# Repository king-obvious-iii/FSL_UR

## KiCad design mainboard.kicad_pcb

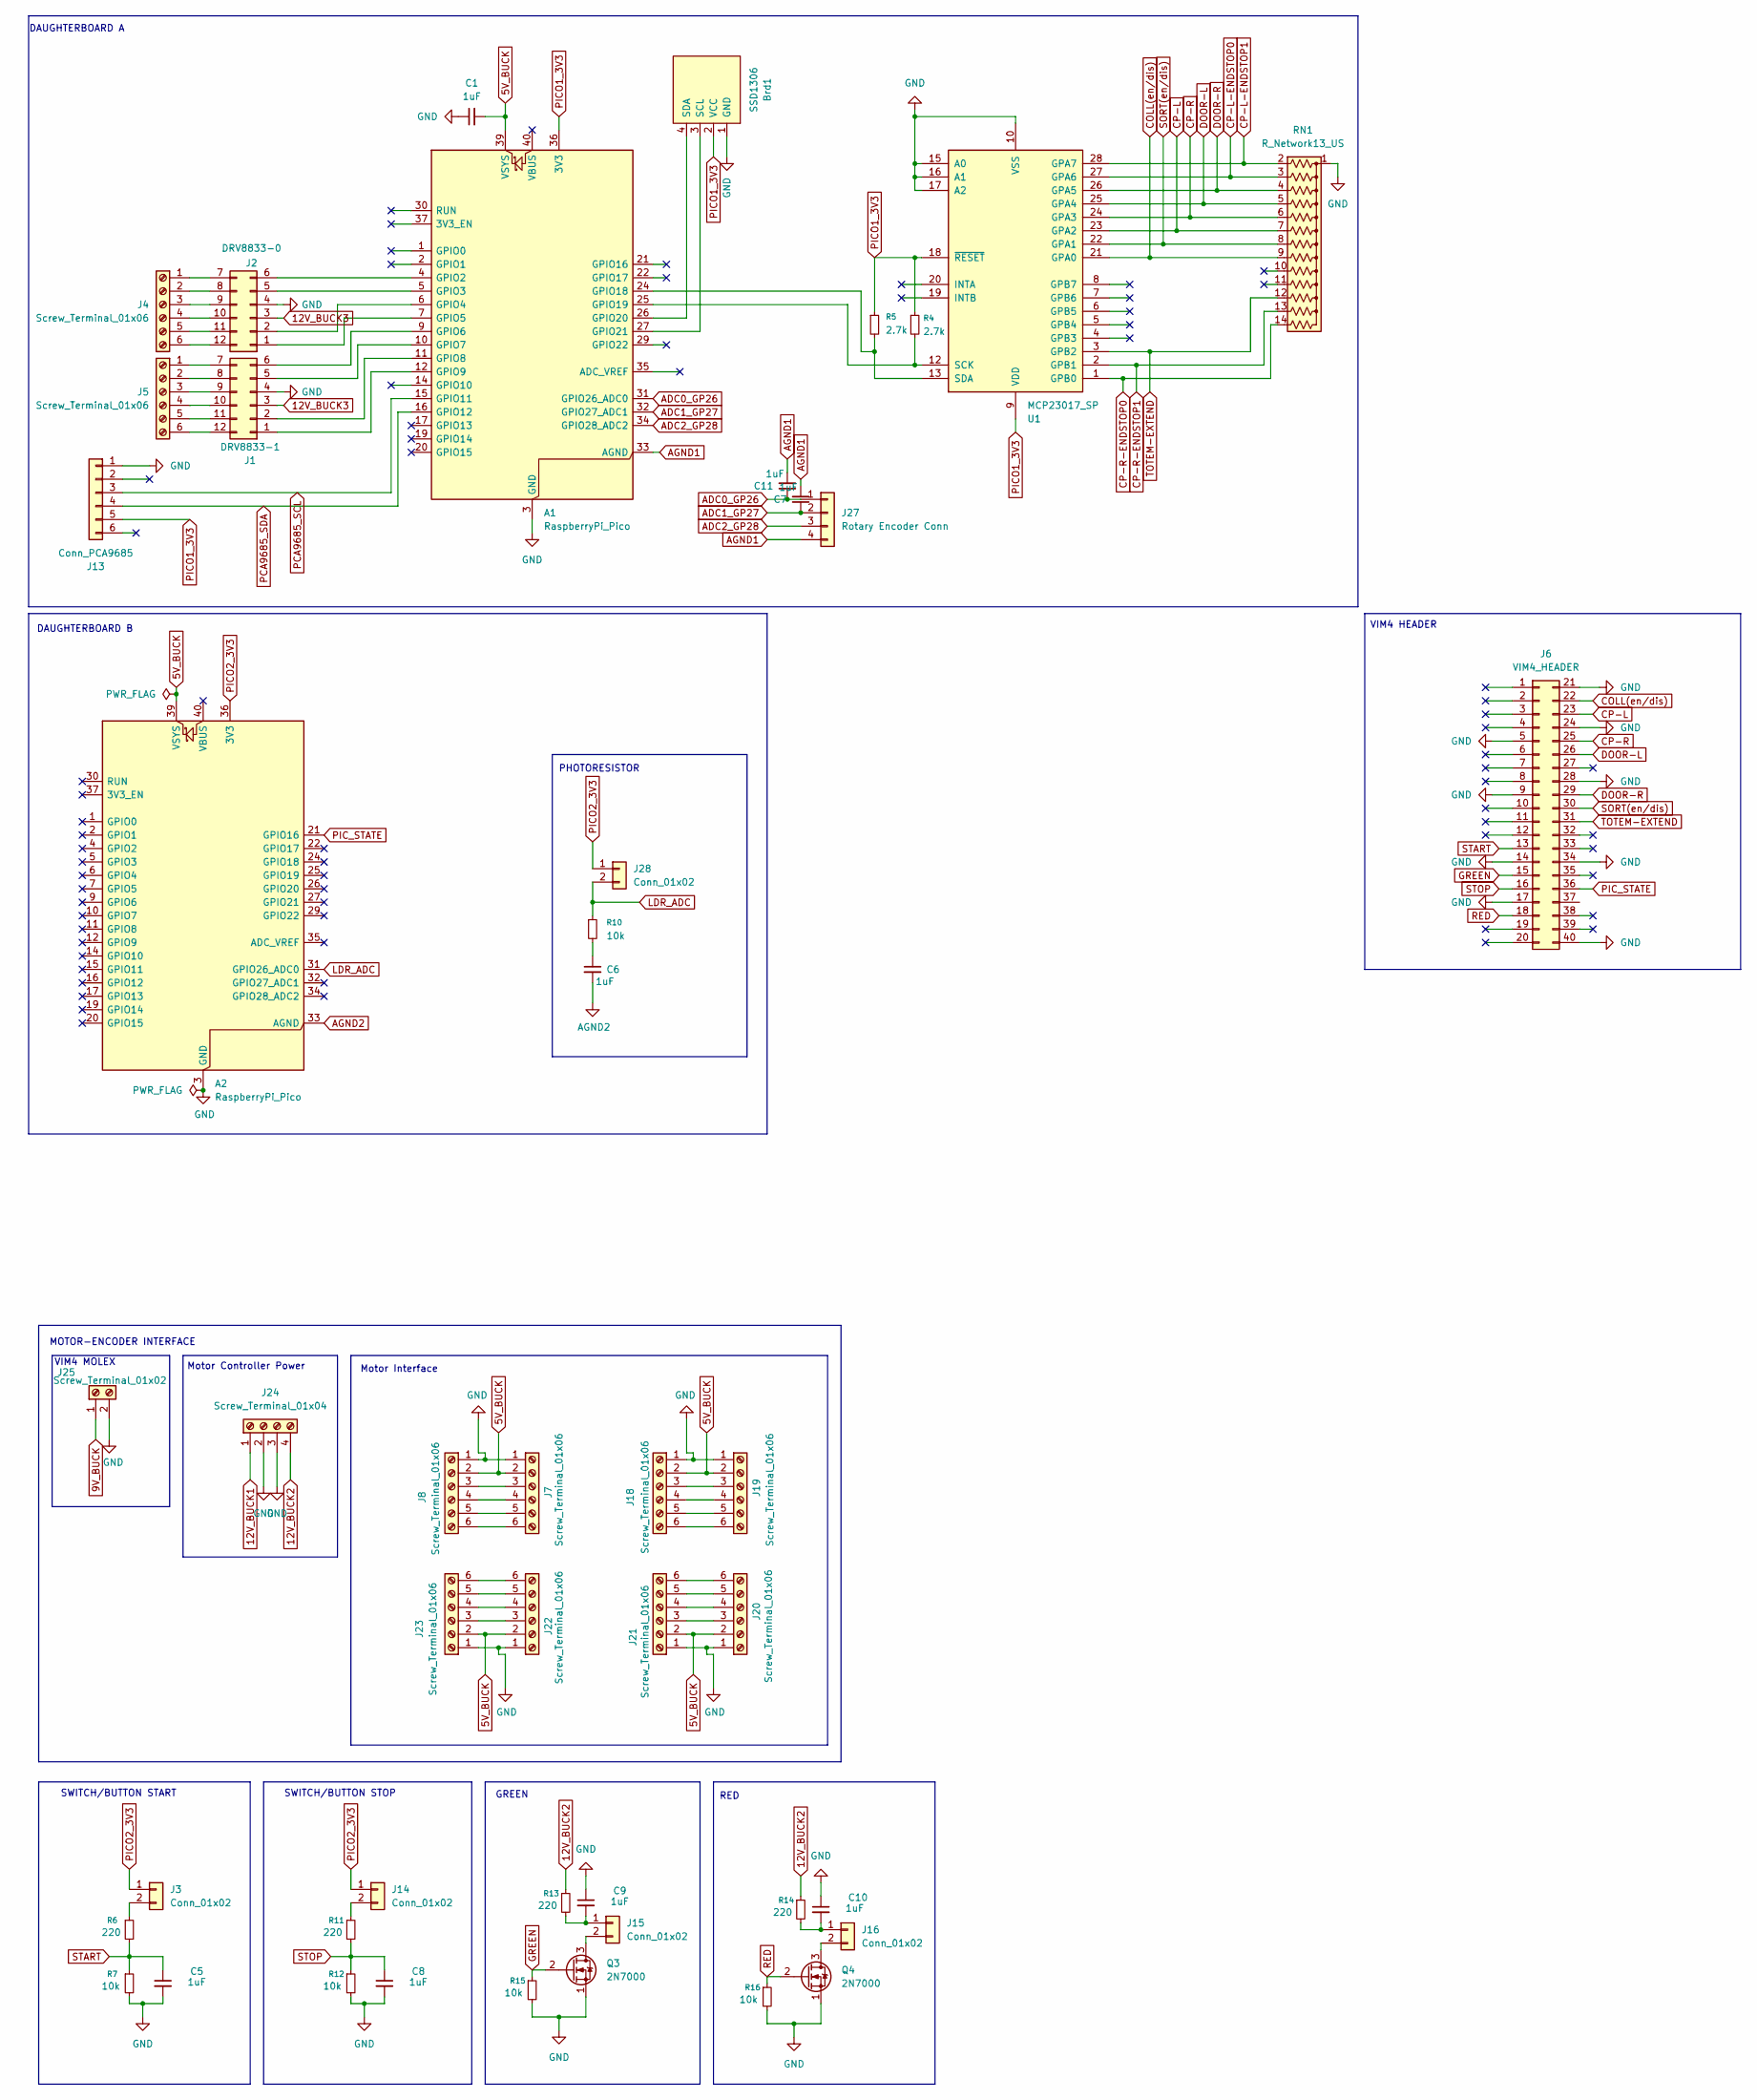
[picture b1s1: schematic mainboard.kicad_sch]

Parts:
A1, A2: RaspberryPi_Pico; RaspberryPi_Pico_Common_Unspecified
Brd1: SSD1306; Molex_KK-254_AE-6410-04A_1x04_P2.54mm_Vertical
C1, C5, C6, C7, C8, C9, C10, C11: 1uF; C_0805_2012Metric
J1: DRV8833-1; DRV8833
J2: DRV8833-0; DRV8833
J3, J14, J15, J16: Conn_01x02; PinHeader_1x02_P2.54mm_Vertical
J4, J5, J7, J8, J18, J19, J20, J21, J22, J23: Screw_Terminal_01x06; TerminalBlock_Xinya_XY308-2.54-6P_1x06_P2.54mm_Horizontal
J6: VIM4_HEADER; IDC-Header_2x20_P2.54mm_Vertical
J13: Conn_PCA9685; JST_EH_B6B-EH-A_1x06_P2.50mm_Vertical
J24: Screw_Terminal_01x04; PinHeader_1x04_P2.54mm_Vertical
J25: Screw_Terminal_01x02; PinHeader_1x02_P2.54mm_Vertical
J27: Rotary Encoder Conn; JST_EH_B4B-EH-A_1x04_P2.50mm_Vertical
J28: Conn_01x02; JST_EH_B2B-EH-A_1x02_P2.50mm_Vertical
Q3, Q4: 2N7000; TO-92_Inline
R4, R5: 2.7k; R_0805_2012Metric
R6, R11, R13, R14: 220; R_0805_2012Metric
R7, R10, R12, R15, R16: 10k; R_0805_2012Metric
RN1: R_Network13_US; DIP-14_W7.62mm
U1: MCP23017_SP; DIP-28_W7.62mm

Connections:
5V_BUCK: A1.39 (VSYS), A2.39 (VSYS), C1.2, J7.2, J8.2, J18.2, J19.2, J20.2, J21.2, J22.2, J23.2; also elsewhere on the board
5V_BUCK2: J13.6
9V_BUCK: J25.1; also elsewhere on the board
12V_BUCK1: J24.1
12V_BUCK2: J24.4, R13.1, R14.1
12V_BUCK3: J1.3, J2.3
ADC0_GP26: A1.31 (GPIO26_ADC0), C11.1, J27.1
ADC1_GP27: A1.32 (GPIO27_ADC1), C7.1, J27.2
ADC2_GP28: A1.34 (GPIO28_ADC2), J27.3
AGND1: A1.33 (AGND), C7.2, C11.2, J27.4
AGND2: A2.33 (AGND), C6.2
COLL(en/dis): J6.22, RN1.9 (R8), U1.21 (GPA0)
CP-L: J6.23, RN1.7 (R6), U1.23 (GPA2)
CP-L-ENDSTOP0: RN1.3 (R2), U1.27 (GPA6); also elsewhere on the board
CP-L-ENDSTOP1: RN1.2 (R1), U1.28 (GPA7); also elsewhere on the board
CP-R: J6.25, RN1.6 (R5), U1.24 (GPA3)
CP-R-ENDSTOP0: RN1.14 (R13), U1.1 (GPB0); also elsewhere on the board
CP-R-ENDSTOP1: RN1.13 (R12), U1.2 (GPB1); also elsewhere on the board
DOOR-L: J6.26, RN1.5 (R4), U1.25 (GPA4)
DOOR-R: J6.29, RN1.4 (R3), U1.26 (GPA5)
GND: A1.3 (GND), A1.8 (GND), A1.13 (GND), A1.18 (GND), A1.23 (GND), A1.28 (GND), A1.38 (GND), A2.3 (GND), A2.8 (GND), A2.13 (GND), A2.18 (GND), A2.23 (GND), A2.28 (GND), A2.38 (GND), Brd1.1 (GND), C1.1, C5.2, C8.2, C9.1, C10.1, J1.4, J2.4, J6.5, J6.9, J6.14, J6.17, J6.21, J6.24, J6.28, J6.34, J6.40, J7.1, J8.1, J13.1, J18.1, J19.1, J20.1, J21.1, J22.1, J23.1, J24.2, J24.3, J25.2, Q3.1 (S), Q4.1 (S), R7.2, R12.2, R15.2, R16.2, RN1.1 (common), U1.10 (VSS), U1.15 (A0), U1.16 (A1), U1.17 (A2); also elsewhere on the board
GREEN: J6.15, Q3.2 (G), R15.1
LDR_ADC: A2.31 (GPIO26_ADC0), J28.2, R10.1
unnamed: A1.4 (GPIO2), J2.6
unnamed: A1.5 (GPIO3), J2.5
unnamed: A1.6 (GPIO4), J2.2
unnamed: A1.7 (GPIO5), J2.1
unnamed: A1.9 (GPIO6), J1.6
unnamed: A1.10 (GPIO7), J1.5
unnamed: A1.11 (GPIO8), J1.2
unnamed: A1.12 (GPIO9), J1.1
unnamed: A1.24 (GPIO18), R5.2, U1.13 (SDA)
unnamed: A1.25 (GPIO19), R4.2, U1.12 (SCK)
unnamed: A1.26 (GPIO20), Brd1.4 (SDA)
unnamed: A1.27 (GPIO21), Brd1.3 (SCL)
unnamed: C6.1, R10.2
unnamed: J1.7, J5.1
unnamed: J1.8, J5.2
unnamed: J1.9, J5.3
unnamed: J1.10, J5.4
unnamed: J1.11, J5.5
unnamed: J1.12, J5.6
unnamed: J2.7, J4.1
unnamed: J2.8, J4.2
unnamed: J2.9, J4.3
unnamed: J2.10, J4.4
unnamed: J2.11, J4.5
unnamed: J2.12, J4.6
unnamed: J3.2, R6.1
unnamed: J7.3, J8.3
unnamed: J7.4, J8.4
unnamed: J7.5, J8.5
unnamed: J7.6, J8.6
unnamed: J14.2, R11.1
unnamed: C9.2, J15.1, R13.2
unnamed: J15.2, Q3.3 (D)
unnamed: C10.2, J16.1, R14.2
unnamed: J16.2, Q4.3 (D)
unnamed: J18.3, J19.3
unnamed: J18.4, J19.4
unnamed: J18.5, J19.5
unnamed: J18.6, J19.6
unnamed: J20.3, J21.3
unnamed: J20.4, J21.4
unnamed: J20.5, J21.5
unnamed: J20.6, J21.6
unnamed: J22.3, J23.3
unnamed: J22.4, J23.4
unnamed: J22.5, J23.5
unnamed: J22.6, J23.6
PCA9685_SCL: A1.15 (GPIO11), J13.3
PCA9685_SDA: A1.16 (GPIO12), J13.4
PIC_STATE: A2.21 (GPIO16), J6.36
RED: J6.18, Q4.2 (G), R16.1
SORT(en/dis): J6.30, RN1.8 (R7), U1.22 (GPA1)
START: C5.1, J6.13, R6.2, R7.1
STOP: C8.1, J6.16, R11.2, R12.1
TOTEM-EXTEND: J6.31, RN1.12 (R11), U1.3 (GPB2)

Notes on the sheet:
DAUGHTERBOARD A
Motor Controller Power
VIM4 MOLEX
PHOTORESISTOR
GREEN
Motor Interface
MOTOR-ENCODER INTERFACE
VIM4 HEADER
RED
DAUGHTERBOARD B
SWITCH/BUTTON STOP
SWITCH/BUTTON START

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
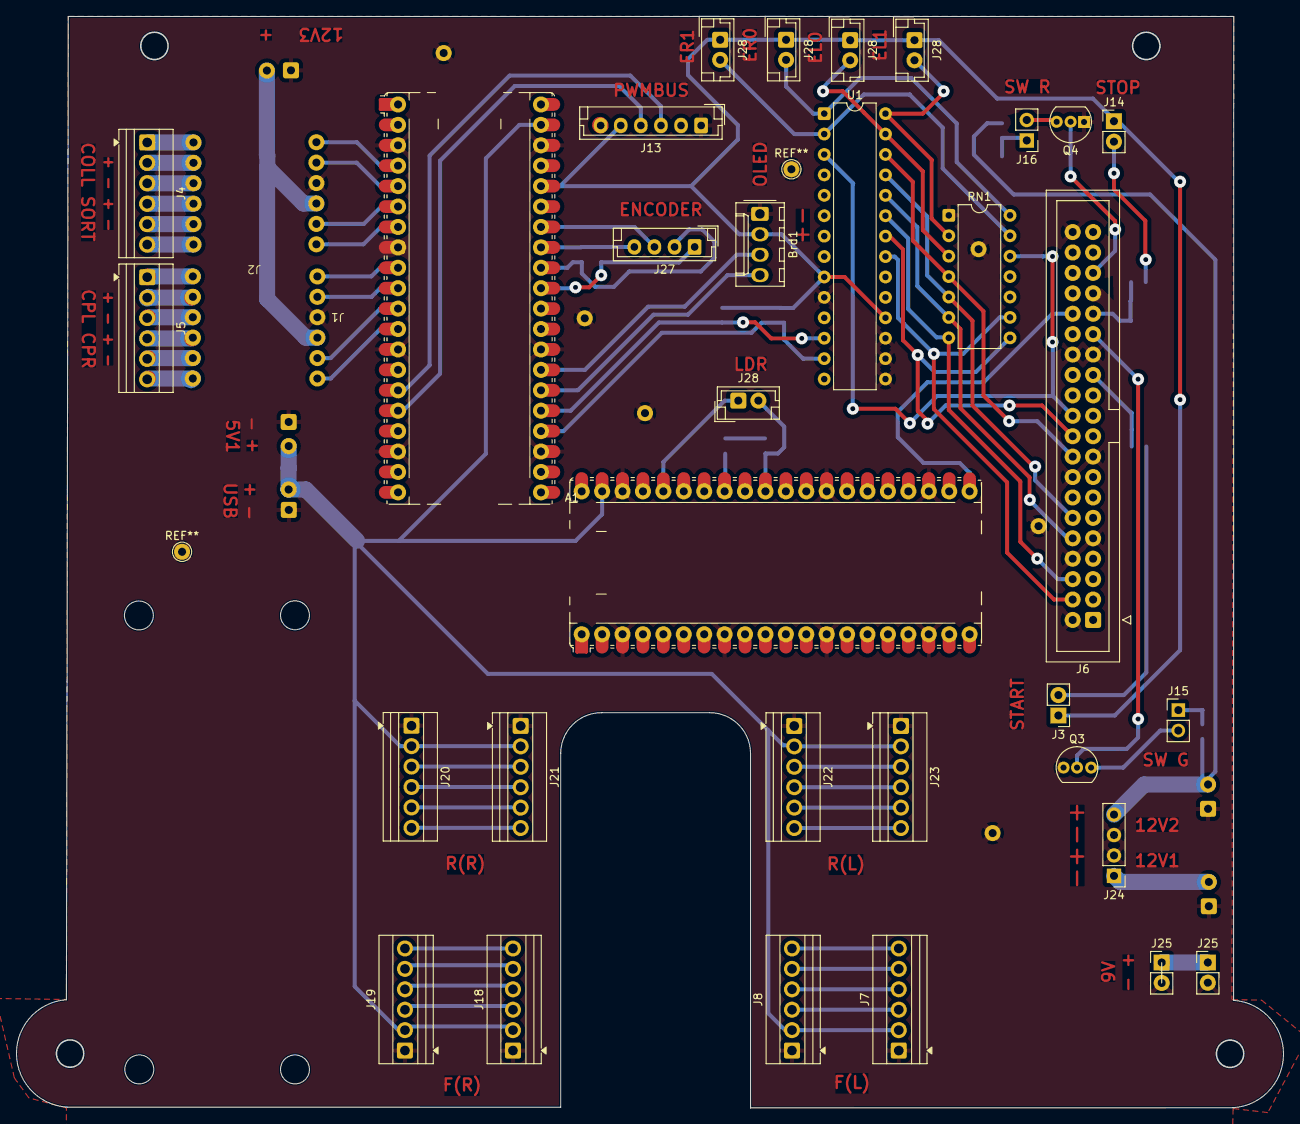
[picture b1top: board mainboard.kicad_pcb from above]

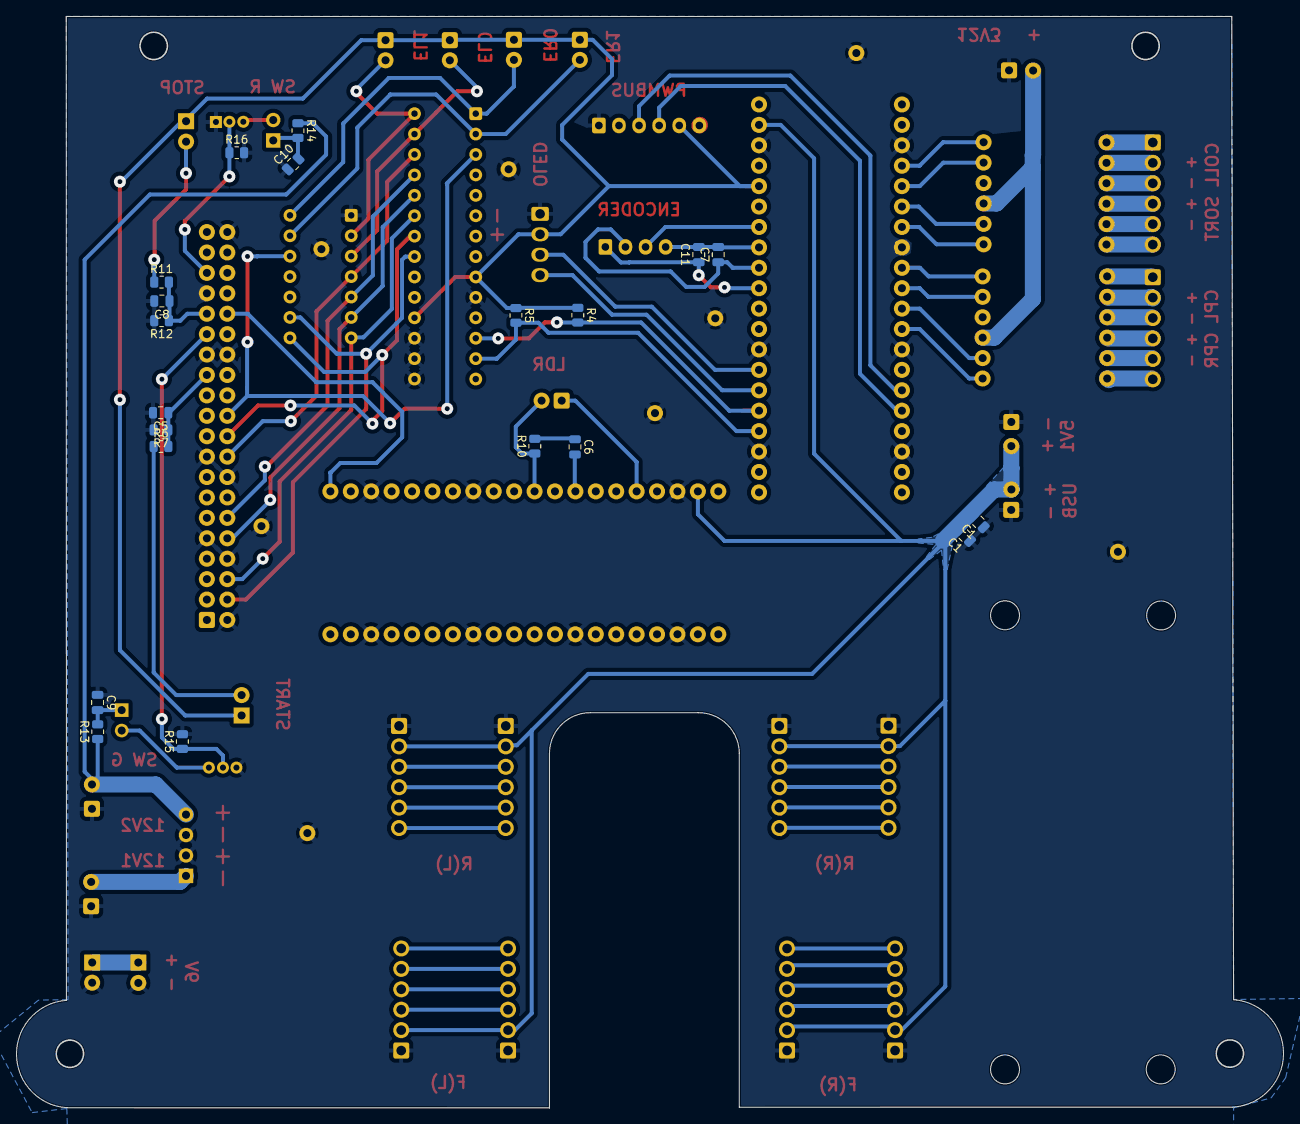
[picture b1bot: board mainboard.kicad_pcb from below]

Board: 2 copper layers, 157.5 x 135.7 mm, 54 parts (20 on the bottom side), 78 nets.

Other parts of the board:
C1#2: 1uF; C_0805_2012Metric
J25#2: Screw_Terminal_01x02; PinHeader_1x02_P2.54mm_Vertical
J28#2, J28#3, J28#4, J28#5: Conn_01x02; JST_EH_B2B-EH-A_1x02_P2.50mm_Vertical

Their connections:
5V_BUCK: C1#2.2; also elsewhere on the board
9V_BUCK: J25#2.1; also elsewhere on the board
CP-L-ENDSTOP0: J28#2.2; also elsewhere on the board
CP-L-ENDSTOP1: J28#3.2; also elsewhere on the board
CP-R-ENDSTOP0: J28#5.2; also elsewhere on the board
CP-R-ENDSTOP1: J28#4.2; also elsewhere on the board
GND: C1#2.1, J25#2.2; also elsewhere on the board

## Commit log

2025-12-13 Mainboard schematics
2025-12-15 Added LDR circuit
2025-12-15 Bucks added
    Bucks added, nets modified to match these buck names
2025-12-15 Added PCB
    Added PCB and DRV8833 footprint.
    Error checked circuit for footprints to PCB
2025-12-15 General reorganization
2025-12-16 Settings import
    Imported settings for traces and routing,
    Placing and organizing PCB components into modules
2025-12-16 Circuit adjustments / PCB component Grouping
    Removed resistor on LDR in schem. Changed to 10k resistor. Added hole distance for PCA9685, SSD1309. Grouped components. Awaiting PIC_FOR_ADC from Dustin
2025-12-27 PIC16F819-ISO Added
    Added PIC, changed footprint to match our 18pin SMD.
    LDR circuit and connection to VIM4 need to be made
2025-12-29 Rearrangement and first pour
    Modified the order of operations for terminal block to fuse to buck. Added a few things like the holes for the Roboclaws, removed the display, since we're going to wire it using a JST connector in or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
    I still need to check with Dustin and make sure that the VIM4 connection to the PIC is the one we want to use.
    I also need to know the exact dimensions of the PCB constraint we are designing this for.
2025-12-30 Peripheral footprint blanks and boundaries
    Peripheral footprint blanks and boundaries added
2026-01-02 Switches updated
    Enumerated all switches in the VIM header and added their respective sub-circuitry. Fixed a few errors I was getting when I updated PCB from schematic.
2026-01-02 Fixed ERC complaints
    Fixed the power and NC complaints issues when I tried to run the ERC check
2026-01-09 The Great Simplification
    Schematic:
    Pico2 added, 12V buck added, Motor-Encoder Interface Added, PIC removed.
    *No work yet on PCB, will chip away at orienting objects tomorrow.
2026-01-10 First full buildup for the PCB
    Board1, bucks removed. Motor interface added,
2026-01-10 Buckboard initial
    Dimensioned bucks.
    Placed DCF of cornpush nonmag bin face where bucks will live.
2026-01-11 0 Error DRC mainboard V1
    completed digital rules check and electrical rules check. ready to export to gerber
2026-01-12 0 Error DRC mainboard V1.1
    Little edits
2026-01-12 0 Error DRC mainboard V1.15
    Placed motor interface within boundaries, rounded off edge.cuts with some arcs.
    resized all of the pads to 2mm
    got rid of some islands and their associated vias.
    ***This version has the chassis DXF in the PCB editor.
2026-01-15 Validated mainboard V1.15
    0 Error 0 Warnings
    Ready for Ochoa chack
2026-01-17 Buckboard Beta 1
    Ready for Ochoa review
2026-01-17 Displayboard added
    V1 of displayboard, this includes the SSD1309 and EC11 Rotary encoder with 1x04 JST connectors at 2.5mm pitch
2026-01-23 V1.2
2026-01-31 Ready boards
    powerboard, displayboard and mainboard all ready to mill
